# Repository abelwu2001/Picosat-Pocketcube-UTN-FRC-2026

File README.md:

# PocketQube PoCat: análisis, ensayos y propuestas de mejora

Este repositorio reúne la documentación, los diseños electrónicos y los resultados del estudio del satélite **PocketQube PoCat**. El trabajo parte de un diseño existente y busca identificar mejoras comprobables mediante simulaciones, mediciones y comparaciones con la versión original.

> [!IMPORTANT]
> Antes de modificar una placa, hay que confirmar su revisión, función, compatibilidad mecánica y relación con las demás placas del satélite. Todos los cambios deben realizarse sobre una copia del diseño original.

## Objetivos del proyecto

- Comprender el funcionamiento completo del PocketQube.
- Identificar la función y las conexiones de cada placa.
- Reunir los resultados obtenidos por los desarrolladores del diseño original.
- Detectar limitaciones reales mediante mediciones o simulaciones.
- Seleccionar una mejora técnicamente justificable.
- Comparar el comportamiento del diseño original con el modificado.
- Documentar el procedimiento y los resultados para que puedan reproducirse.

## Configuración del satélite

### Placas y elementos principales

| Carpeta o placa | Función principal | Uso en la configuración |
|---|---|---|
| `pq_obc_comms` | Computadora de a bordo y comunicación LoRa | Se utiliza |
| `pq_eps` | Gestión de energía, MPPT, batería y distribución de tensiones | Se utiliza |
| `pq_adcs` | Determinación y control de actitud | A seleccionar (hay dos para eligir) |
| `pq_ymag_board` | Magnetorquer del eje Y | Se utiliza |
| `pq_latboard` | Placas laterales con panel solar y sensores; una incorpora la antena | Se utilizan varias unidades |
| `pq_botboard` | Placa inferior, panel solar, batería, umbilical y *killswitches* | Se utiliza |
| `pq_botnotsobot` | Placa inferior deslizante o estructural del conjunto | Se utiliza |
| `pq_pl1` | Payload de cámara VGA | A seleccionar |
| `pq_pl2` | Payload de detección RFI en banda L | A seleccionar |
| `pq_topboard` | Placa superior genérica | Alternativa al payload, según la configuración |
| `pq_egse` | Equipo eléctrico de apoyo y pruebas en tierra | No vuela |
| `assembly` | Modelos y archivos del ensamblaje mecánico | Solo documentación/diseño |

> [!WARNING]
> Puede cambiar.

## Orden funcional del sistema

El recorrido general de energía, control y datos puede resumirse así:

1. Los paneles solares entregan energía a la `pq_eps`.
2. La EPS administra la carga de la batería y alimenta las demás placas.
3. La `pq_obc_comms` controla el satélite y transmite o recibe información.
4. La `pq_adcs` mide y controla la orientación mediante sensores y magnetorquers.
5. La `pq_pl2` realiza las mediciones de interferencia en banda L.

## Posibles líneas de mejora

### 1. Mejorar el sistema de energía

- Aumentar la eficiencia de los convertidores.
- Revisar el funcionamiento del MPPT.
- Reducir el rizado de las alimentaciones.
- Mejorar el diseño térmico y las pistas de potencia.
- Disminuir las emisiones de las etapas conmutadas.

### 2. Mejorar el sistema de comunicaciones

- Optimizar la adaptación de la antena a `50 Ω`.
- Revisar la pista RF y su camino de retorno.
- Reducir armónicos del transmisor.
- Mejorar el mecanismo de despliegue.
- Comparar alcance, potencia y sensibilidad.

### 3. Mejorar el control de actitud

- Calibrar magnetómetro, giróscopo y sensores solares.
- Filtrar ruido y deriva de los sensores.
- Mejorar el algoritmo de estimación y control.
- Optimizar el accionamiento de los magnetorquers.
- Evitar que las bobinas interfieran con el magnetómetro.

### 4. Reducir interferencias electromagnéticas

- Medir el piso de ruido de PL2 en forma aislada.
- Encender cada subsistema por separado para identificar la fuente de ruido.
- Revisar planos de masa y caminos de retorno.
- Agregar filtros, ferritas, desacoplos o blindaje cuando corresponda.
- Evaluar una ventana silenciosa de medición mediante firmware.
- Comparar los espectros antes y después de la modificación.

### 5. Mejorar el payload de cámara

- Aumentar resolución o calidad de imagen.
- Reducir el consumo entre capturas.
- Incorporar memoria o compresión.
- Mejorar el protocolo de transferencia.

## Links de trabajo 

> [!NOTE]
> **Links**
>
> ```text
> Note one:
> Trello: 
> Drive:
> ```

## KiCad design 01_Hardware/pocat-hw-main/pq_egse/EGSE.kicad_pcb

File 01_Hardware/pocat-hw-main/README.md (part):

# IEEE Open PocketQube Kit – Hardware necesario

Este documento resume las placas, elementos estructurales,
componentes externos, cableado y tornillería necesarios para
el armado de la plataforma PocketQube.

> Nota:
> No se incluyen aquí payloads específicos de las variantes
> demostradoras de la Wiki. La carga útil se considera un
> subsistema independiente/custom.
>
> Las cantidades se basan principalmente en la documentación
> de montaje y hardware del IEEE Open PocketQube Kit.
> Algunas revisiones del repositorio y de la Wiki presentan
> pequeñas diferencias, por lo que siempre debe comprobarse
> la revisión final de PCB antes de comprar componentes.

Link de la wiki donde se explica todo sobre el proyecto:
 
>https://wiki.nanosatlab.space/shelves/ieee-open-pocketqube-kit-mFR

Link BOM final

>https://docs.google.com/spreadsheets/d/18evn2hEh3wvYzuJMzKZhzkFULgpysAK2np7i2tM_1j0/edit?gid=1567048071#gid=1567048071

# 1. PLACAS PCB

## 1.1 Placas del PocketQube

| **Cantidad** | **Placa** | **Función** |
|---:|---|---|
| 1 | **PQ_ADCS_HBridge** | Control de actitud: recibe sensores y maneja los magnetorquers mediante puentes H. |
| 1 | **PQ_EPS** | Sistema de potencia: recibe energía solar, carga la batería y distribuye las tensiones del satélite. |
| 1 | **pq_obc_comms** | Computadora principal + comunicaciones por radio con tierra. |
| 1 | **pq_topboard** | Cara superior estructural e interfaz de la zona del payload. |
| 1 | **pq_botboard** | Cara inferior; integra celda solar, sensores y un magnetorquer eje -Y PCB. |
| 4 | **pq_latboard** | Caras laterales +X, -X, +Z y -Z. Integran celda solar, sensores y magnetorquer; una lleva además la antena COMMS. |
| 1 | **PQ_MagYBoard** | Magnetorquer interno dedicado al eje +Y. |
| 1 | **pq_botnotsobot** | Placa mecánica asociada al sliding/deployer y al sistema de despliegue. |
| **11** | **Total PCBs del conjunto** | Sin contar payload custom ni EGSE. |

### Magnetorquers

El PocketQube utiliza **6 magnetorquers**:

- 4 integrados en las `pq_latboard`
- 1 integrado en la `pq_botboard`
- 1 en la `PQ_MagYBoard`

Los magnetorquers integrados en las placas se forman mediante
pistas/bobinas de cobre del propio PCB, por lo que no se compran
como componentes independientes.

## 1.2 Placa de soporte en tierra

## Cableado e interconexiones

| ID | From | Num. of cables | Connector | To | Num. of cables | Connector | Length (mm) |
|---:|---|---:|---|---|---:|---|---:|
| 1 | Lat +Z | 10 | PicoBlade | PCB Connector | 10 | PicoBlade | |
| 2 | PCB Connector | 10 | PicoBlade | ADCS | 10 | PicoClasp | |
| 3 | Lat -Z | 10 | PicoBlade | PCB Connector | 10 | PicoBlade | |
| 4 | PCB Connector | 10 | PicoBlade | ADCS | 10 | PicoClasp | |
| 5 | Lat +X | 10 | PicoBlade | PCB Connector | 10 | PicoBlade | |
| 6 | PCB Connector | 10 | PicoBlade | ADCS | 10 | PicoClasp | |
| 7 | Lat -X | 10 | PicoBlade | PCB Connector | 10 | PicoBlade | |
| 8 | PCB Connector | 10 | PicoBlade | ADCS | 10 | PicoClasp | |
| 9 | Battery | 2 | PicoBlade | - | - | - | |
| 10 | PCB Connector | 2 | PicoBlade | Bottom Board | 2 | PicoBlade | |
| 11 | Battery Heater & NTC | 3 | PicoClasp | - | - | - | |
| 12 | PCB Connector | 3 | PicoClasp | ADCS | 3 | PicoClasp | |
| 13 | Umbilical | 8 | PicoBlade | PCB Connector | 8 | PicoBlade | |
| 14 | Bottom Board | 15 | PicoBlade | PCB Connector | 15 | PicoBlade | |
| 15 | PCB Connector | 15 | PicoBlade | ADCS | 15 | PicoClasp | |
| 16 | Top Board | 9 | PicoBlade | PCB Connector | 9 | PicoBlade | |
| 17 | PCB Connector | 9 | PicoBlade | ADCS | 9 | PicoClasp | |

La EGSE no forma parte del hardware de vuelo. Se utiliza en banco
para alimentación, mediciones, depuración e integración.

Por lo tanto:

- PCBs del PocketQube: 11
- PCB EGSE: 1
- Total a fabricar si se realiza todo el conjunto: 12

# 2. BATERÍA

| Cantidad | Elemento | Especificación |
|---:|---|---|
| 1 | Batería Li-ion | 3.7 V |
| 1 | Capacidad nominal | 1400 mAh |
| 1 | Energía nominal | 5.18 Wh |
| 1 | Modelo indicado en Assembly Wiki | 103540 |

La batería se instala dentro de la estructura inferior.

IMPORTANTE:
La documentación del proyecto posee revisiones que mencionan
otras baterías. Para este listado se conserva la especificación
indicada en la página de Assembly de la Wiki.

# 3. CELDAS SOLARES

Modelo indicado:

Lightricity S3040_CIC

Características aproximadas indicadas en la Wiki:

- Tecnología: Triple Junction GaAs
- Integración: CIC
- Dimensiones: 40.15 x 30.35 x 0.30 mm
- Área fotovoltaica activa: 12 cm²
- Tensión AM0: ~2.5 V
- Potencia AM0: ~0.5 W

## Cantidad

| Ubicación | Cantidad |
|---|---:|
| Lateral +X | 1 |
| Lateral -X | 1 |
| Lateral +Z | 1 |
| Lateral -Z | 1 |
| Bottom board | 1 |
| **TOTAL** | **5** |

La plataforma utiliza:

**5 x Lightricity S3040_CIC**

La cara superior/payload no lleva celda solar en esta
configuración de la Wiki.

# 4. FOTODIODOS

Modelo indicado:

**SLCD-61N8 – Advanced Photonix**

La arquitectura ADCS utiliza un fotodiodo en cada cara para
determinar la incidencia de radiación solar.

| Ubicación | Cantidad |
|---|---:|
| Cuatro lateral boards | 4 |
| Top board | 1 |
| Bottom board | 1 |
| **TOTAL** | **6** |

Cantidad a comprar:

**6 x SLCD-61N8**

Datos principales indicados en la documentación:

- Isc aproximada: 170 µA
- Voc aproximada: 0.4 V
- Máxima sensibilidad: 930 nm
- Acceptance Half Angle: 60°

# 5. SENSORES DE TEMPERATURA

Modelo:

**TCN75A / TCN75AVOA – Microchip**

La Wiki especifica un sensor de temperatura en cada placa
lateral.

Cantidad mínima documentada para las caras laterales:

**4 x TCN75A**

Características:

- Interfaz: I2C
- Rango: -40 °C a +125 °C
- Precisión: aproximadamente ±1 °C
- Bajo consumo

Verificar en la BOM final de `topboard` y `botboard` si la
revisión fabricada incorpora sensores de temperatura
adicionales.

# 6. KILLSWITCHES

El PocketQube utiliza:

**2 x killswitches**

Los dos interruptores están conectados en serie para proporcionar
redundancia.

Su función es mantener desconectada la batería mientras el
PocketQube se encuentra dentro del deployer.

Cuando el PocketQube es liberado:

1. los killswitches dejan de estar presionados;
2. se habilita la alimentación;
3. comienza la secuencia de encendido.

IMPORTANTE:
La Wiki de Assembly los describe asociados a la estructura/PCB
inferior. El repositorio también contiene `pq_botnotsobot`,
relacionado con la interfaz de despliegue. Confirmar la ubicación
mecánica exacta con la revisión final que se vaya a fabricar.

# 7. SISTEMA DE ANTENA COMMS

Se necesita una placa lateral configurada para comunicaciones.

Elementos principales:

| Cantidad | Elemento |
|---:|---|
| 1 | Antena desplegable de cinta metálica |
| 1 | Cable RF desde OBC-COMMS |
| 1 | Dyneema / UHMWPE |
| 1 | Resorte de extensión |
| 1 | Jumper SMT de guiado |
| 2 | Resistencias thermal-knife |
| 1 | Cable clip / sujeción de antena |
| 2 | Tornillos M2.5 asociados al mecanismo |
| según diseño | Inserts/elementos de fijación |

## Dyneema

Especificación indicada:

- UHMWPE
- diámetro: 0.35 mm
- resistencia aproximada: 26 kg

La documentación de mantenimiento utiliza aproximadamente
40 cm para realizar el montaje, dejando excedente para los
nudos.

## Resorte

Modelo indicado:

**McMaster-Carr 5108N98**

Su función es mantener tensión constante sobre el Dyneema.

## Jumper SMT

Modelo indicado:

**Harwin S1731-46R**

Se utiliza como guía y para mantener el Dyneema en contacto con
los thermal knives.

## Thermal knives

La revisión actual de la página del deployer utiliza:

**2 x resistencias de baja impedancia**

Valor actualmente indicado:

**4.7 ohm**

Estas resistencias son calentadas eléctricamente mediante
`BURNCOMMS`, cortando/fundiendo el Dyneema y permitiendo que la
antena se despliegue.

IMPORTANTE:
Documentación anterior de mantenimiento menciona 7.5 ohm.
Comprobar siempre el esquemático de la revisión fabricada antes
de comprar las resistencias.

# 8. CABLEADO INTERNO

## Laterales ↔ ADCS

Cantidad:

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
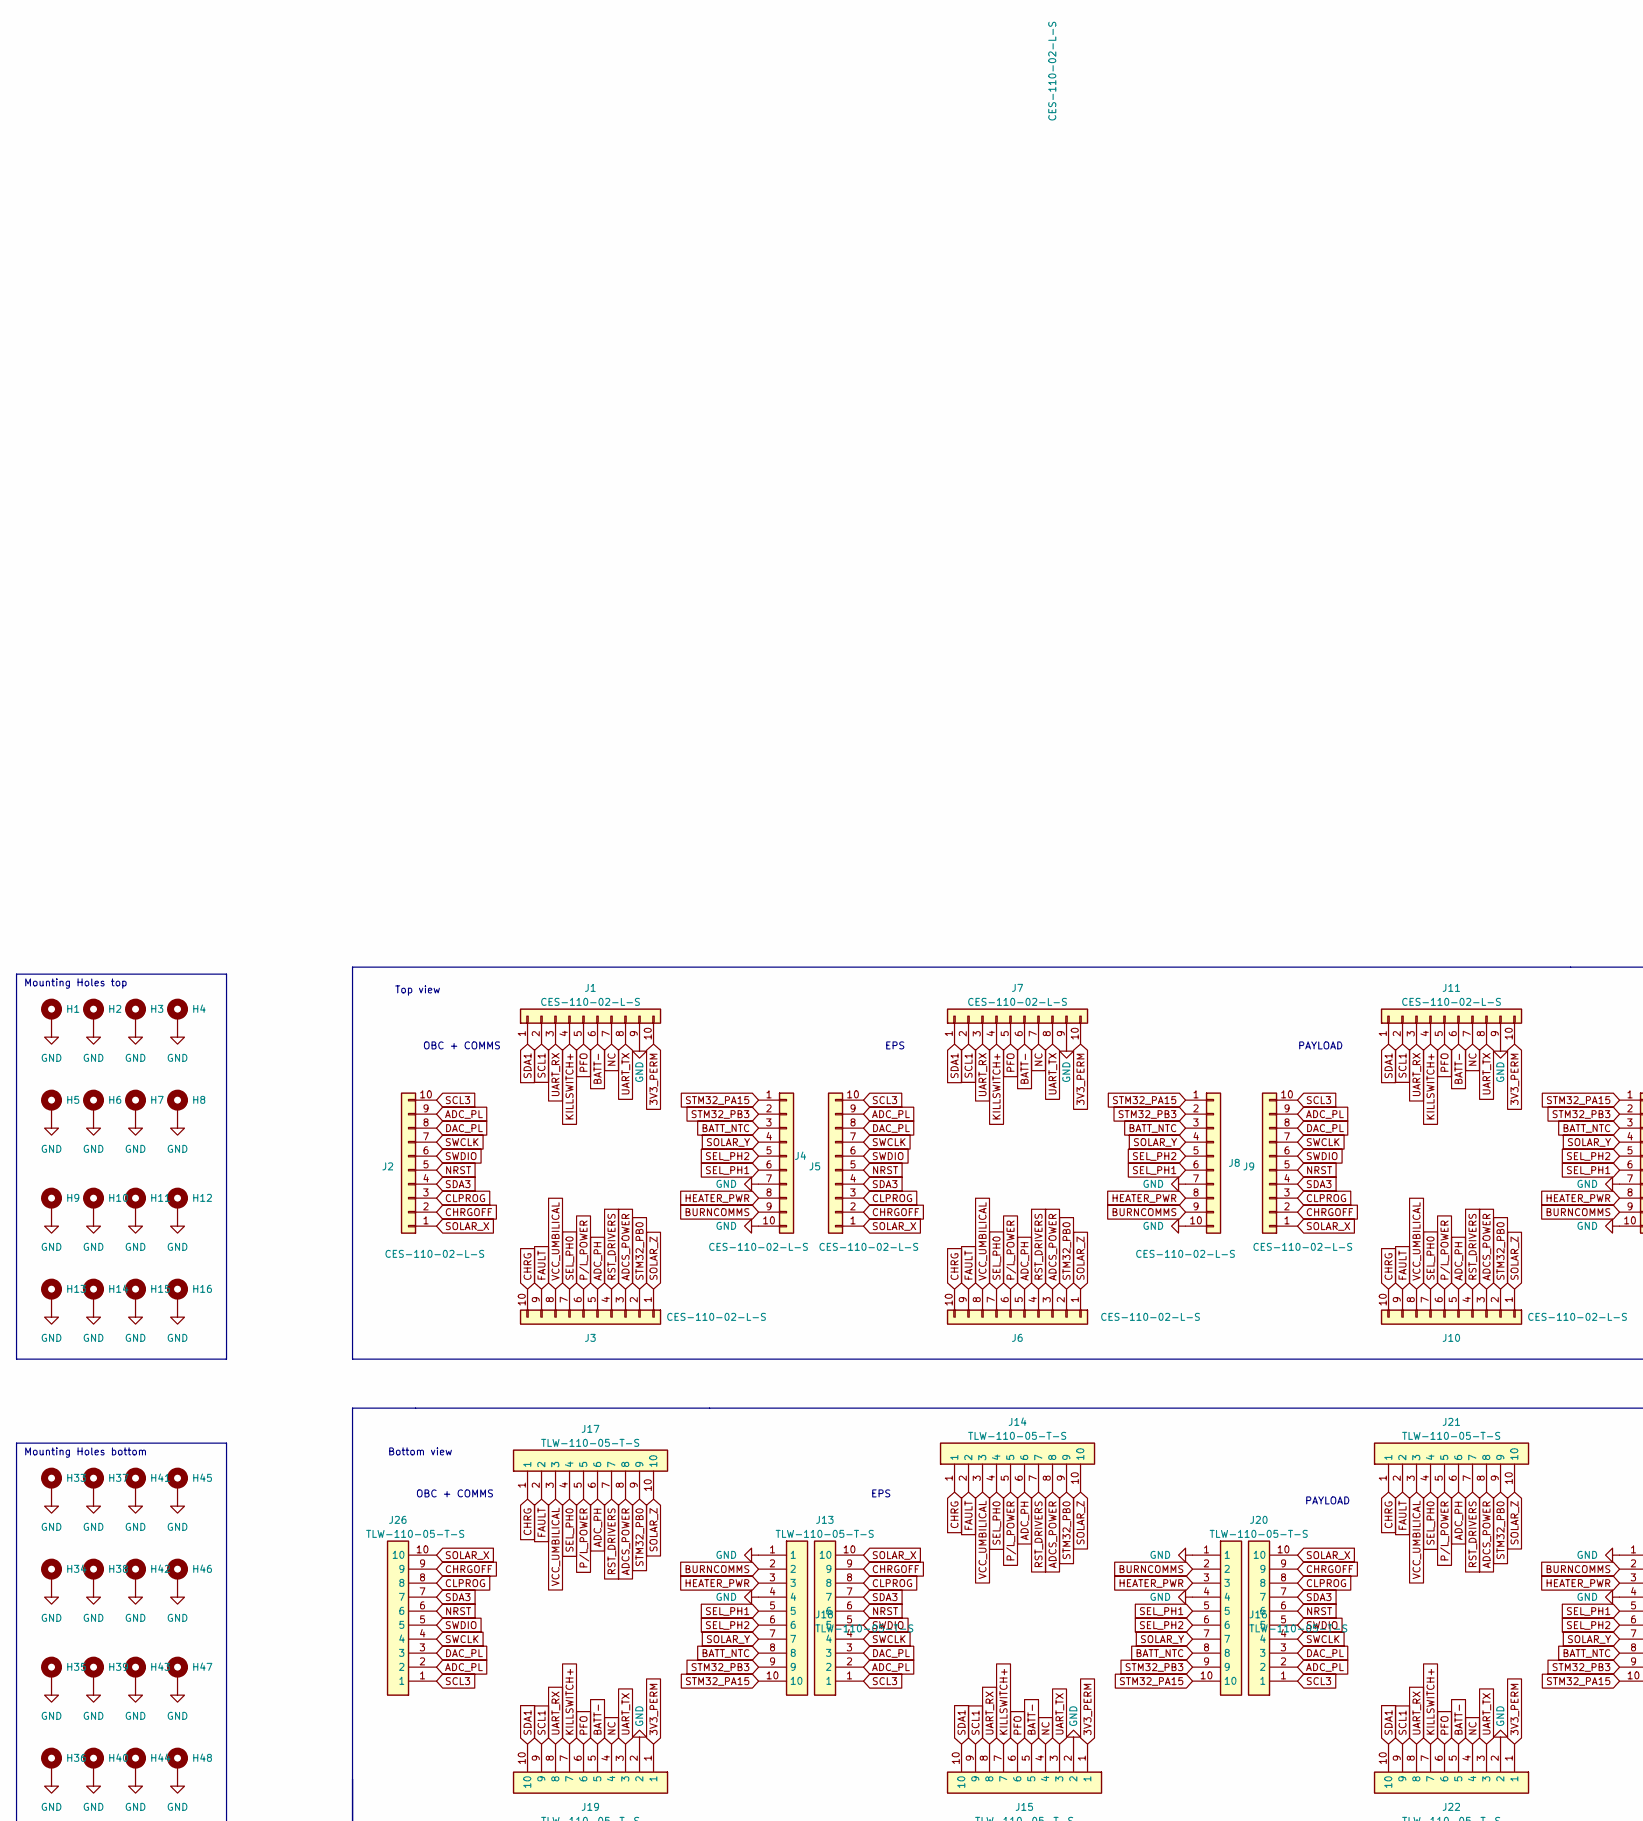
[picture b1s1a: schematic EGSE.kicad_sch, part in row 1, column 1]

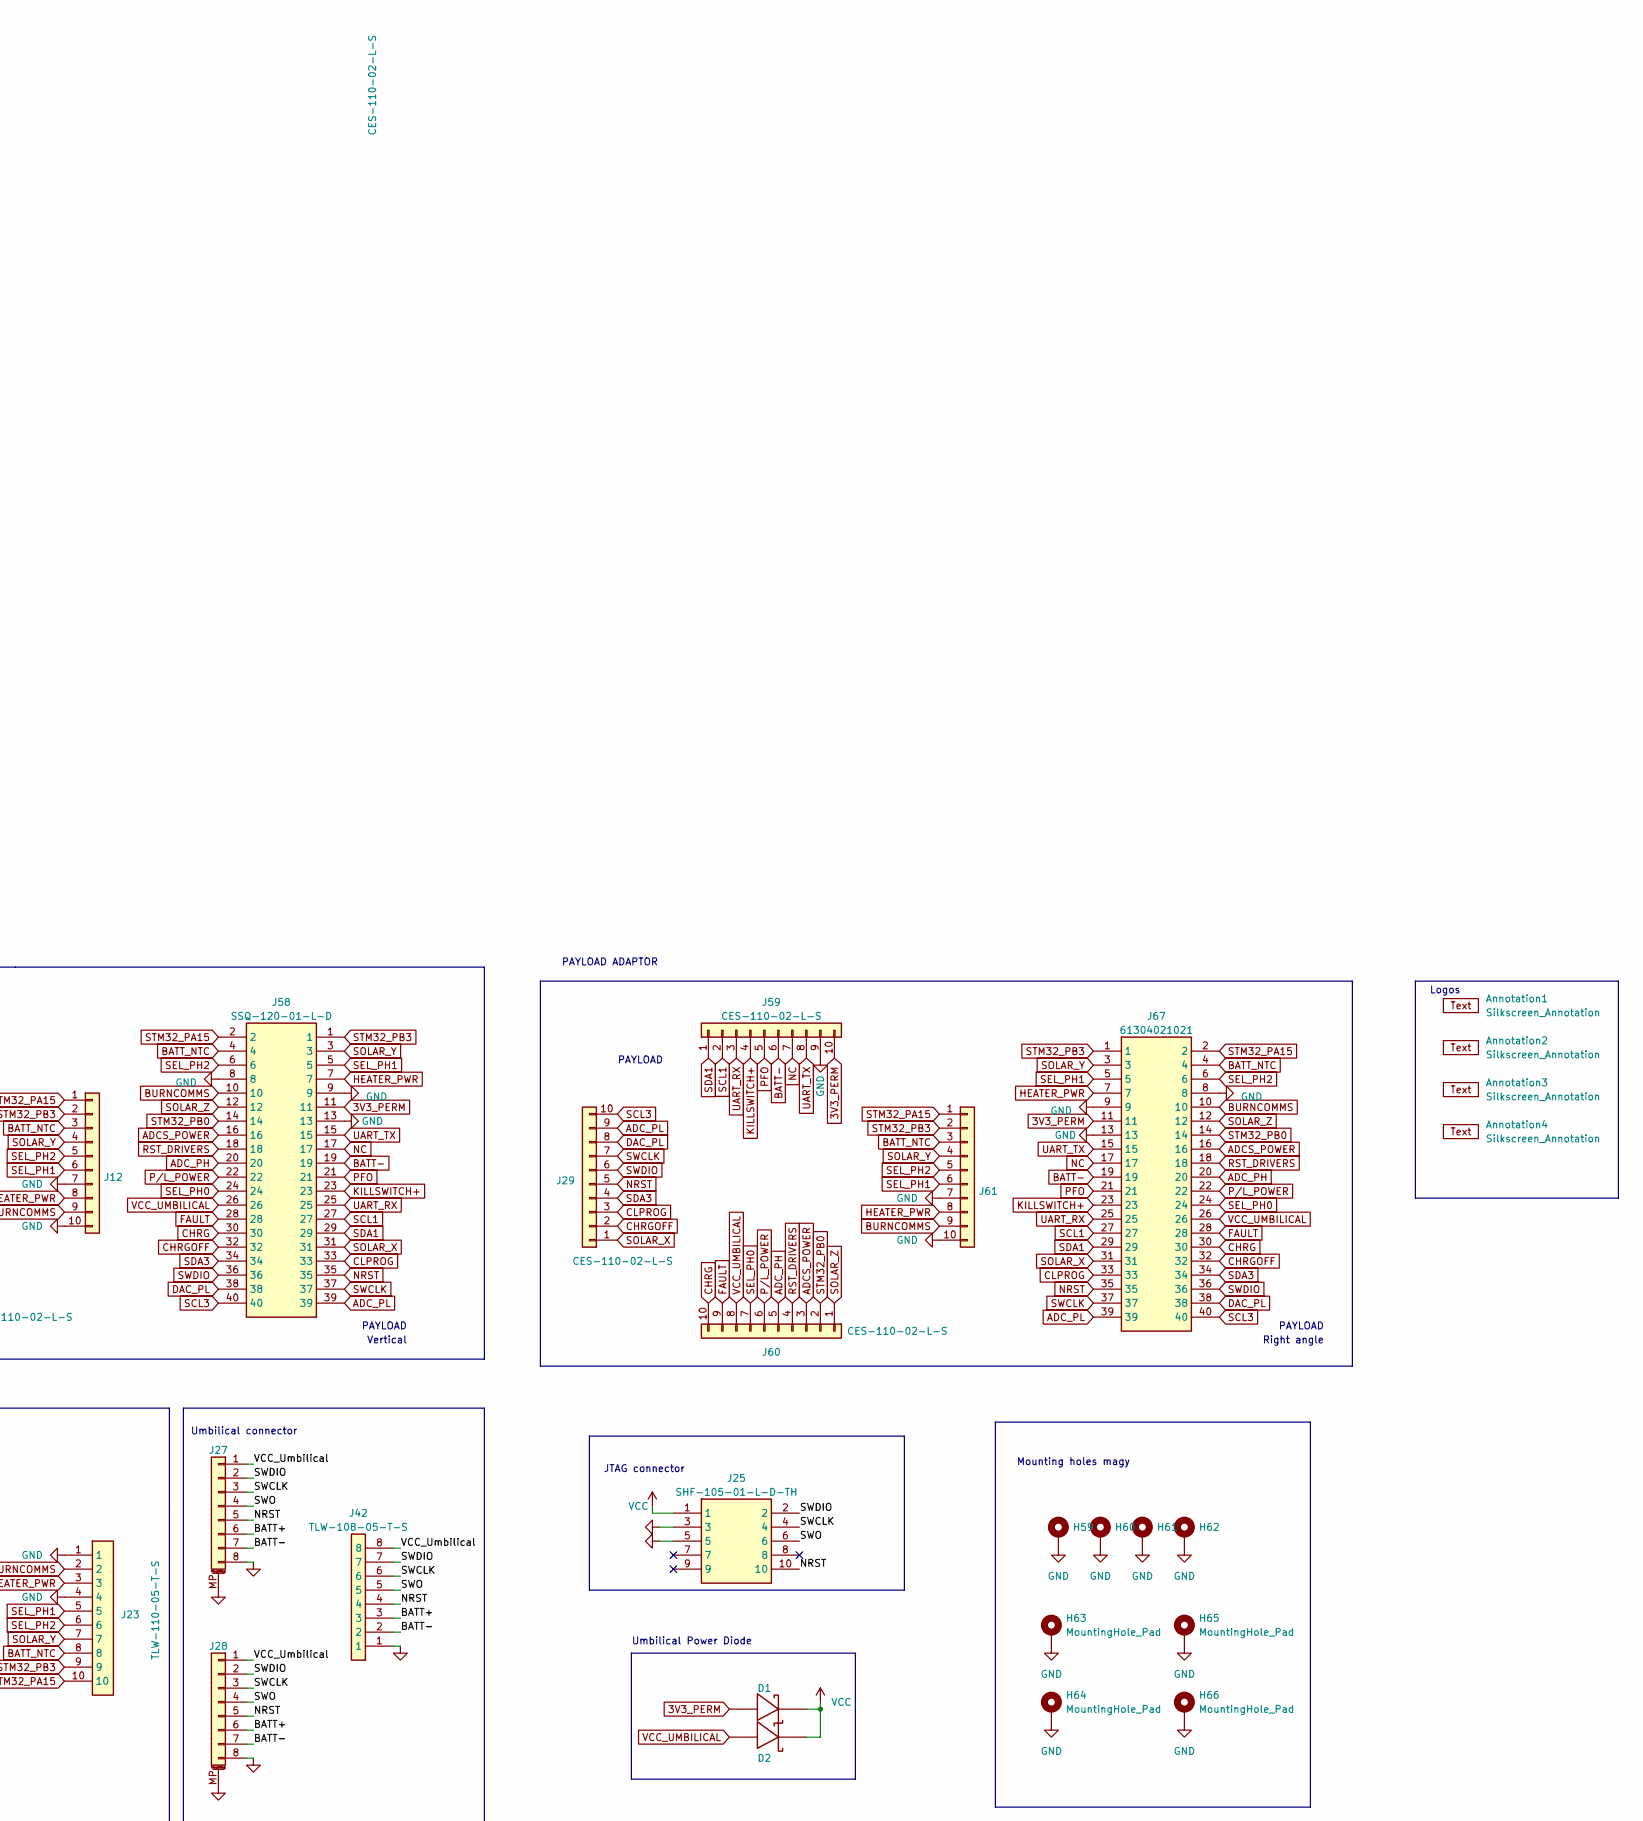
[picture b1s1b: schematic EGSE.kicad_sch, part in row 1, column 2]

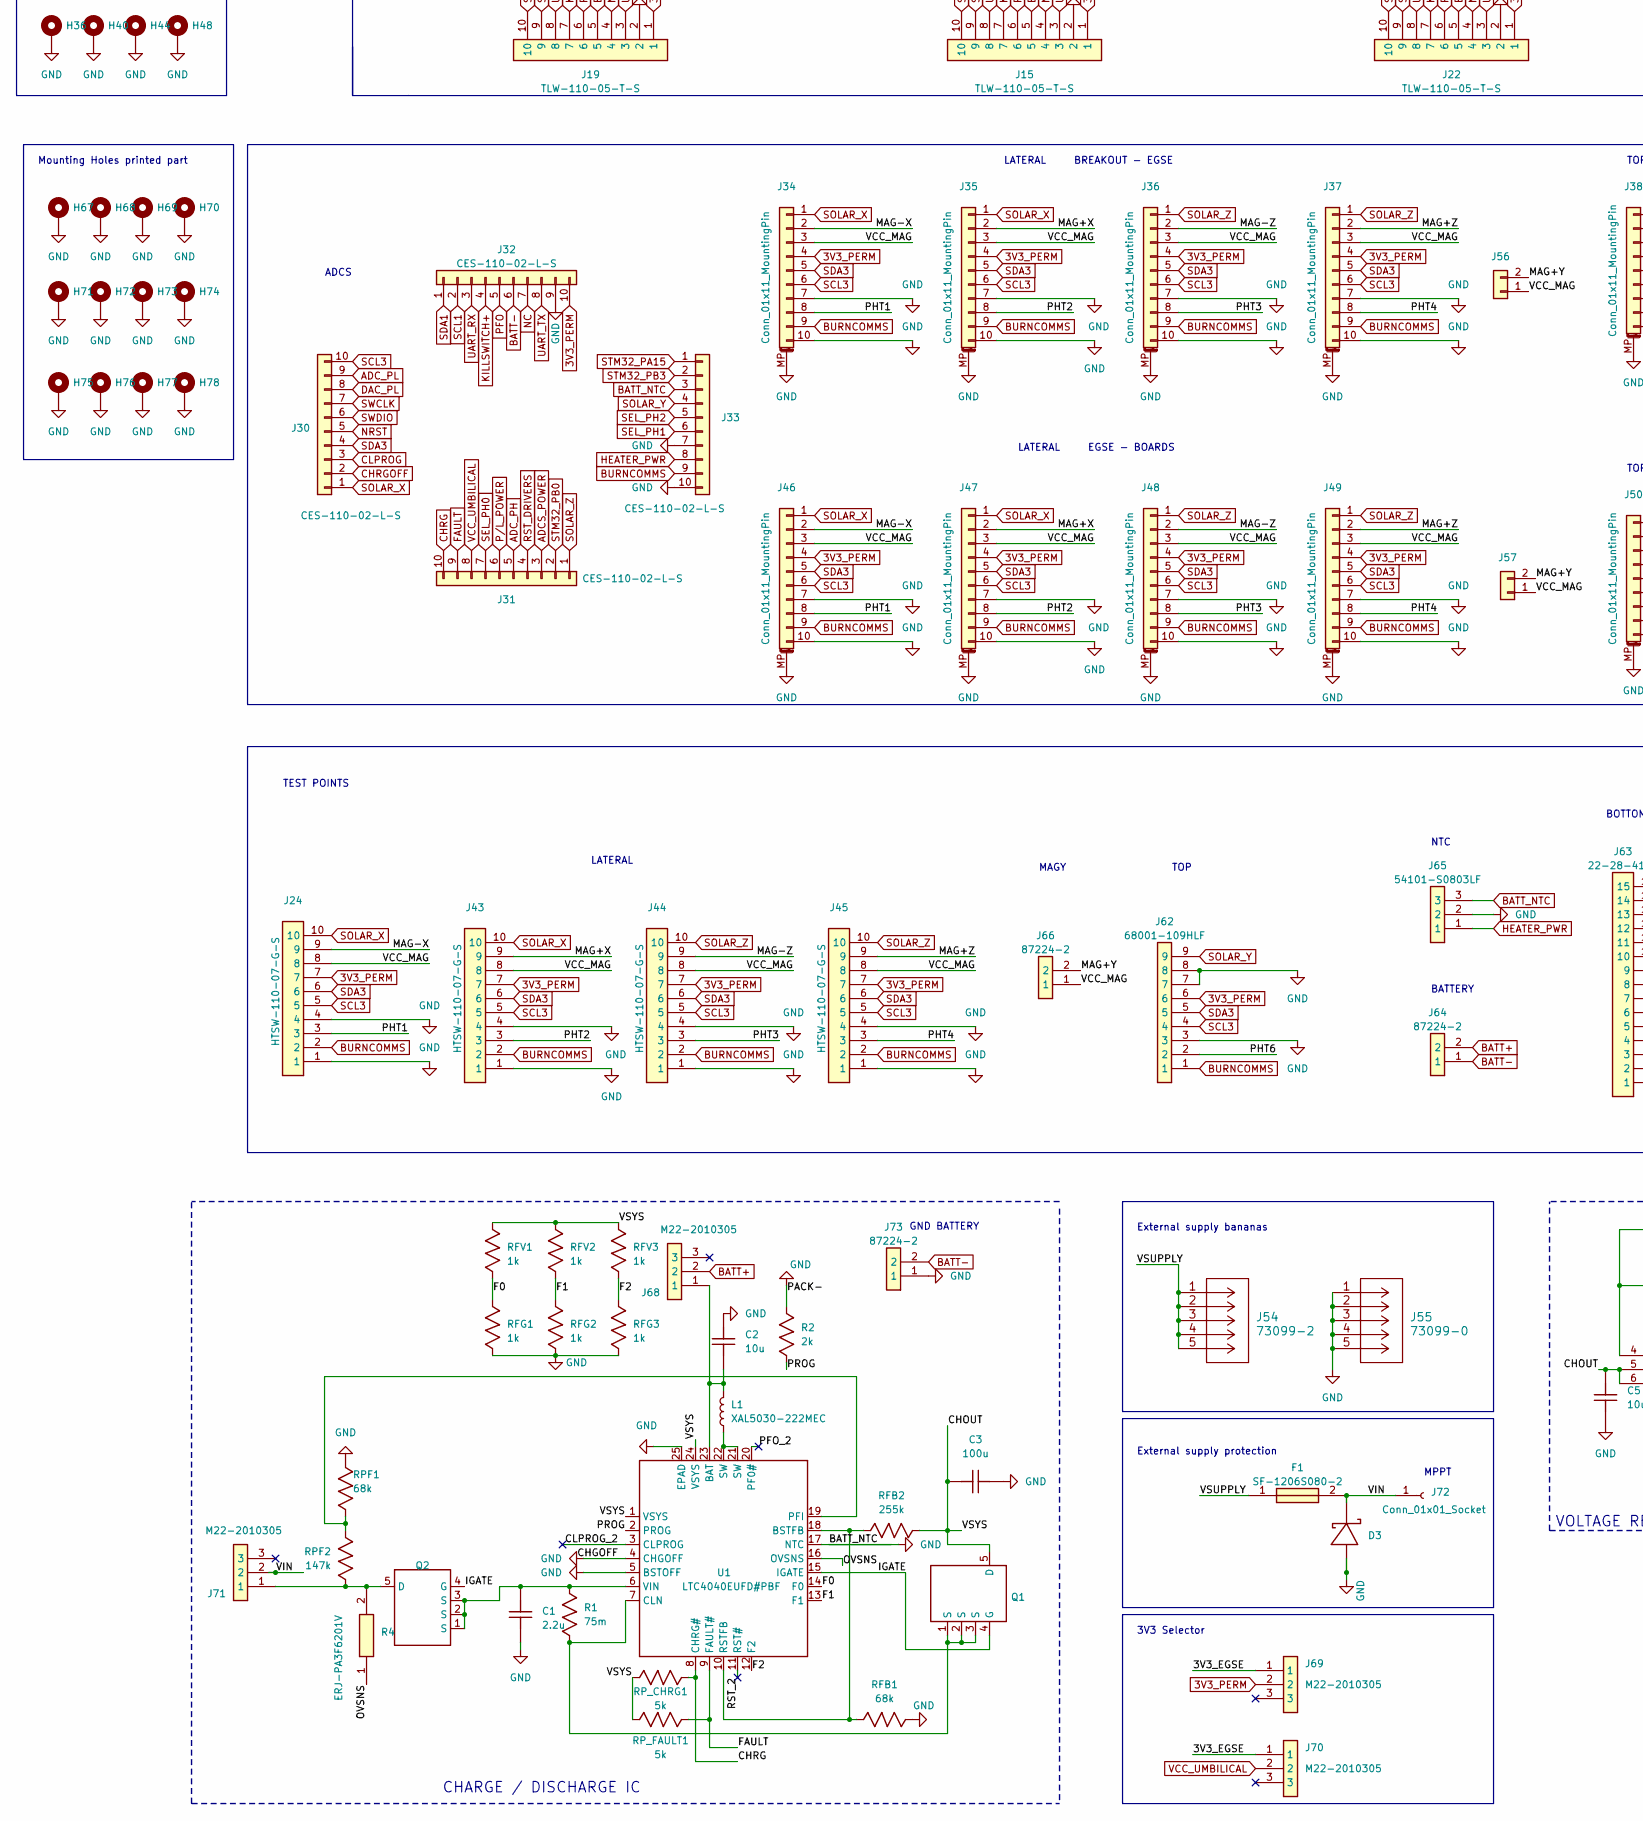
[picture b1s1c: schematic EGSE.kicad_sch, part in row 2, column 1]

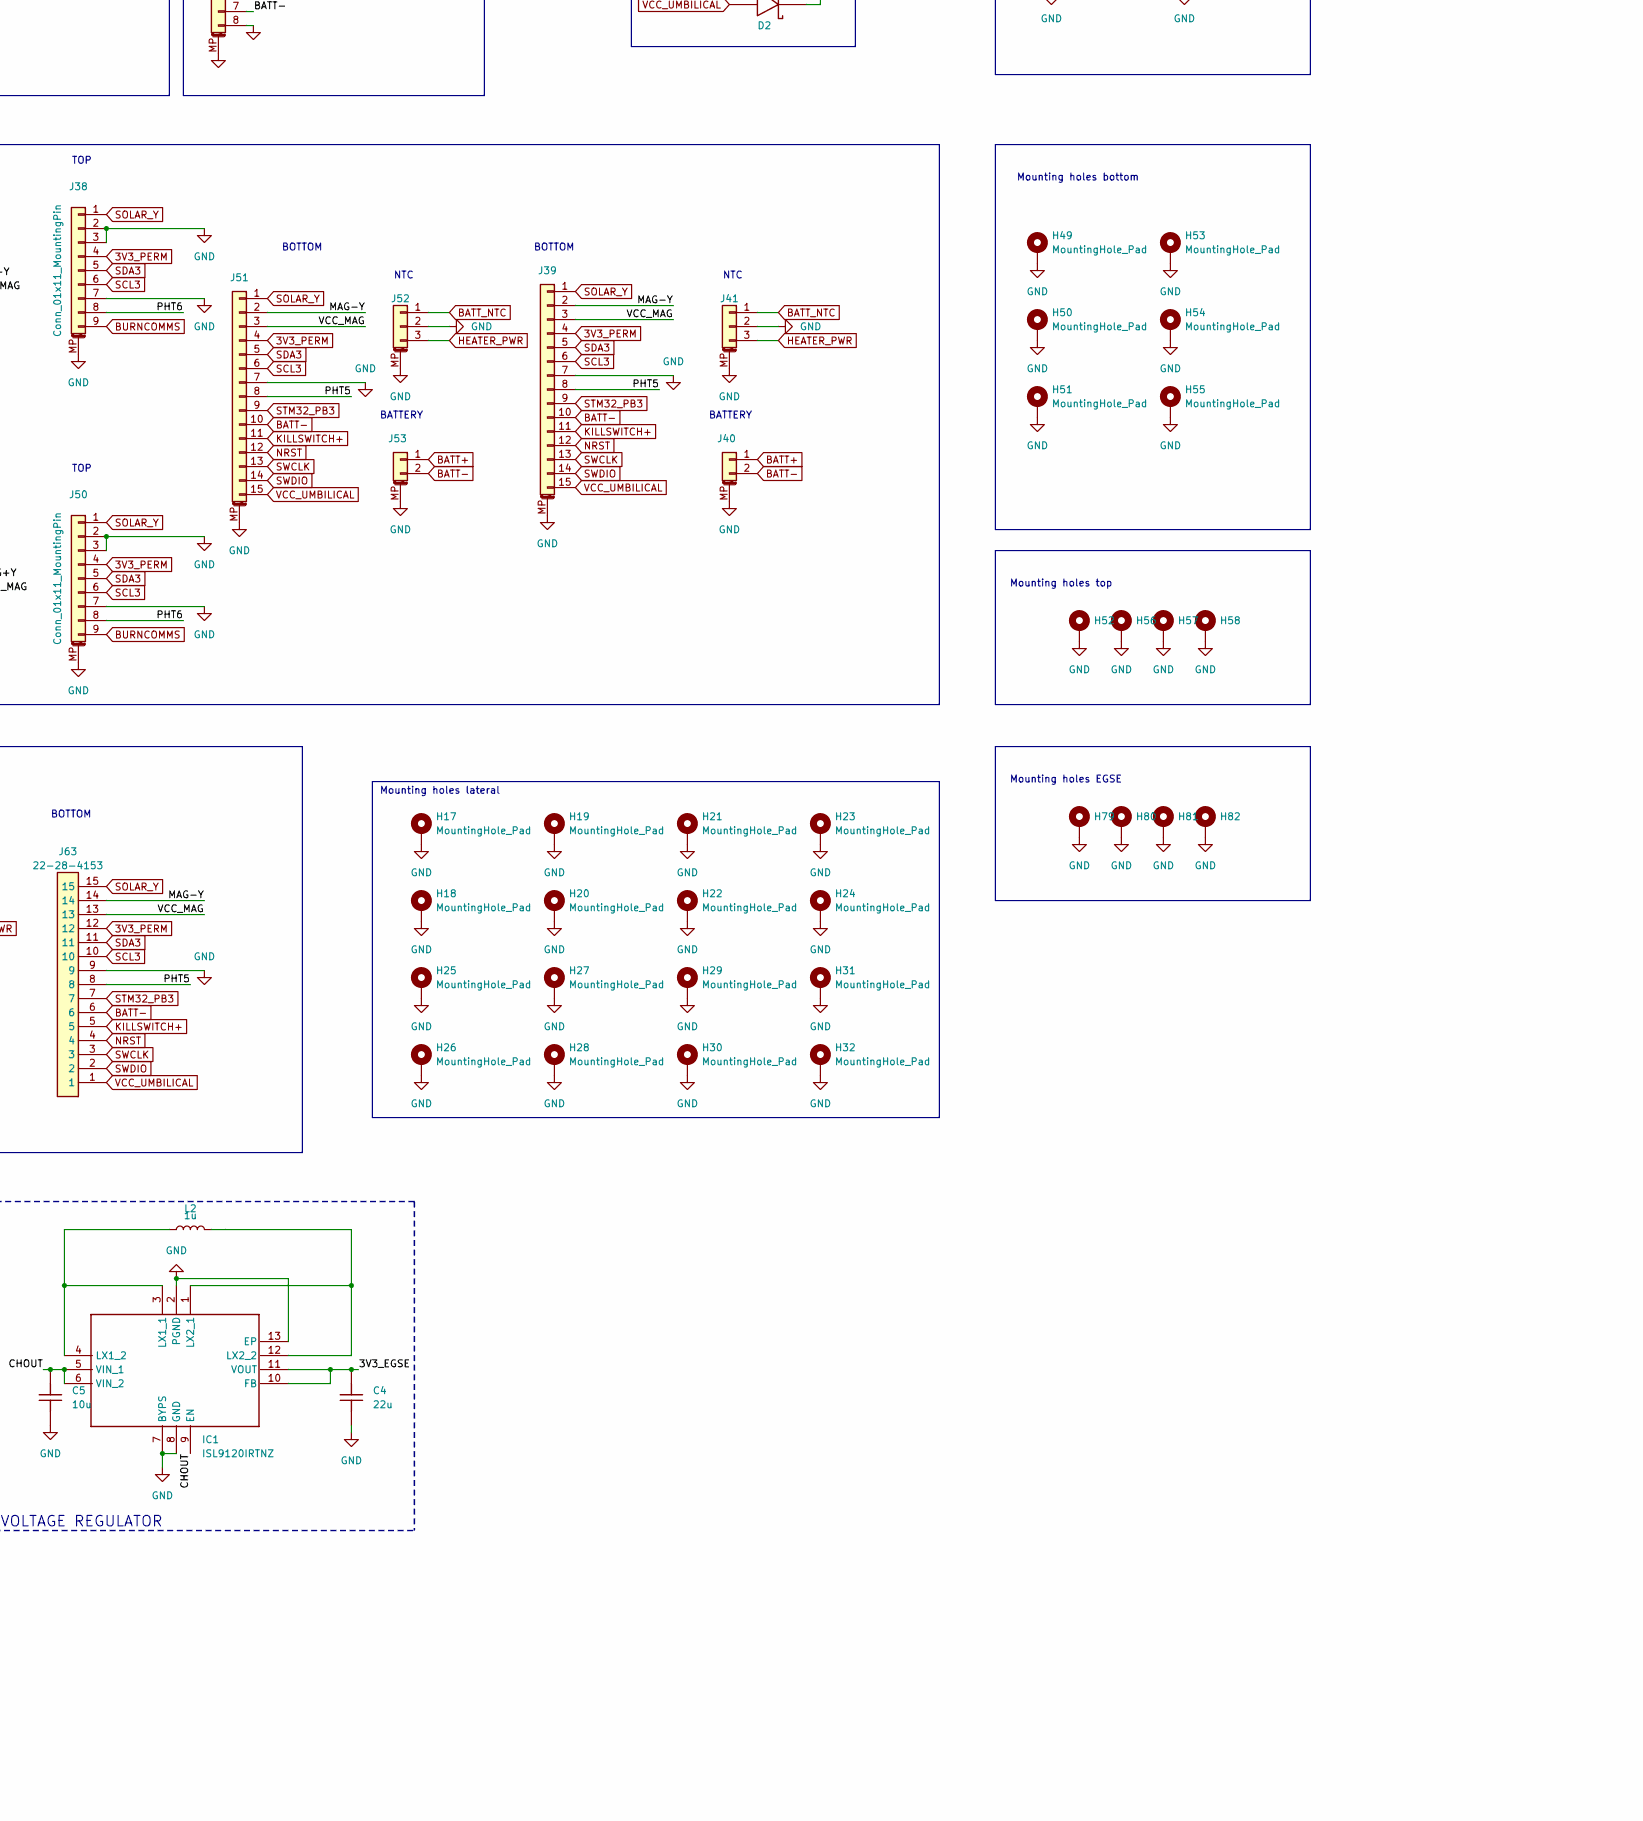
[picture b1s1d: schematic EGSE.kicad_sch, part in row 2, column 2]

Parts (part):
Annotation1: Silkscreen_Annotation; Bridgemaker__Annotation1
Annotation2: Silkscreen_Annotation; IEEE_logo__Annotation2
Annotation3: Silkscreen_Annotation; NSL_long__Annotation3
Annotation4: Silkscreen_Annotation; Telecos__Annotation4
C1: 2.2u; C_0603_1608Metric__C1
C2: 10u; C_0603_1608Metric__C2
C3: 100u; C_1206_3216Metric__C3
C4: 22u; C_0603_1608Metric__C4
C5: 10u; C_0603_1608Metric__C5
D1, D2, D3: type="D" model="RBS1LAM40ATR" lib=""; RBS1LAM40ATR_Schottky; Manufacturer Part Numbe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 RBS1LAM40ATR
F1: SF-1206S080-2; FUSC3116X70N__F1; Mouser Part Number 652-SF-1206S080-2
H1: MountingHole_Pad; MountingHole_3.2mm_M3_Pad__H1
H2: MountingHole_Pad; MountingHole_3.2mm_M3_Pad__H2
H3: MountingHole_Pad; MountingHole_3.2mm_M3_Pad__H3
H4: MountingHole_Pad; MountingHole_3.2mm_M3_Pad__H4
H5: MountingHole_Pad; MountingHole_3.2mm_M3_Pad__H5
H6: MountingHole_Pad; MountingHole_3.2mm_M3_Pad__H6
H7: MountingHole_Pad; MountingHole_3.2mm_M3_Pad__H7
H8: MountingHole_Pad; MountingHole_3.2mm_M3_Pad__H8
H9: MountingHole_Pad; MountingHole_3.2mm_M3_Pad__H9
H10: MountingHole_Pad; MountingHole_3.2mm_M3_Pad__H10
H11: MountingHole_Pad; MountingHole_3.2mm_M3_Pad__H11
H12: MountingHole_Pad; MountingHole_3.2mm_M3_Pad__H12
H13: MountingHole_Pad; MountingHole_3.2mm_M3_Pad__H13
H14: MountingHole_Pad; MountingHole_3.2mm_M3_Pad__H14
H15: MountingHole_Pad; MountingHole_3.2mm_M3_Pad__H15
H16: MountingHole_Pad; MountingHole_3.2mm_M3_Pad__H16
H17, H18, H19, H20, H21, H22, H23, H24, H25, H26, H27, H28, H29, H30, H31, H32, H49, H50, H51, H53, H54, H55, H63, H64, H65, H66: MountingHole_Pad; MountingHole_2.2mm_M2_Pad
H33, H34, H35, H36, H37, H38, H39, H40, H41, H42, H43, H44, H45, H46, H47, H48, H52, H56, H57, H58, H59, H60, H67, H70, H71, H72, H73, H74, H75, H76, H77, H78, H79, H80, H81, H82: MountingHole_Pad; MountingHole_3.2mm_M3_Pad
H61: MountingHole_Pad; MountingHole_3.2mm_M3_Pad__H61
H62: MountingHole_Pad; MountingHole_3.2mm_M3_Pad__H62
H68: MountingHole_Pad; MountingHole_3.2mm_M3_Pad__H68
H69: MountingHole_Pad; MountingHole_3.2mm_M3_Pad__H69
IC1: ISL9120IRTNZ
J1: CES-110-02-L-S; PinSocket_1x10_P2.54mm_Vertical__J1; Manufacturer Part Numbe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 CES-110-02-L-S
J2: CES-110-02-L-S; PinSocket_1x10_P2.54mm_Vertical__J2; Manufacturer Part Numbe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 CES-110-02-L-S
J3: CES-110-02-L-S; PinSocket_1x10_P2.54mm_Vertical__J3; Manufacturer Part Numbe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 CES-110-02-L-S
J4: CES-110-02-L-S; PinSocket_1x10_P2.54mm_Vertical__J4; Manufacturer Part Numbe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 CES-110-02-L-S
J5: CES-110-02-L-S; PinSocket_1x10_P2.54mm_Vertical__J5; Manufacturer Part Numbe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 CES-110-02-L-S
J6: CES-110-02-L-S; PinSocket_1x10_P2.54mm_Vertical__J6; Manufacturer Part Numbe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 CES-110-02-L-S
J7: CES-110-02-L-S; PinSocket_1x10_P2.54mm_Vertical__J7; Manufacturer Part Numbe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 CES-110-02-L-S
J8: CES-110-02-L-S; PinSocket_1x10_P2.54mm_Vertical__J8; Manufacturer Part Numbe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 CES-110-02-L-S
J9: CES-110-02-L-S; PinSocket_1x10_P2.54mm_Vertical__J9; Manufacturer Part Numbe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 CES-110-02-L-S
J10: CES-110-02-L-S; PinSocket_1x10_P2.54mm_Vertical__J10; Manufacturer Part Numbe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 CES-110-02-L-S
J11: CES-110-02-L-S; PinSocket_1x10_P2.54mm_Vertical__J11; Manufacturer Part Numbe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 CES-110-02-L-S
J12: CES-110-02-L-S; PinSocket_1x10_P2.54mm_Vertical__J12; Manufacturer Part Numbe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 CES-110-02-L-S
J13: TLW-110-05-T-S; HDRV10W64P0X254_1X10_2540X248X838P__J13; Mouser Part Number 200-HTSW11007GS
J14: TLW-110-05-T-S; HDRV10W64P0X254_1X10_2540X248X838P__J14; Mouser Part Number 200-HTSW11007GS
J15: TLW-110-05-T-S; HDRV10W64P0X254_1X10_2540X248X838P__J15; Mouser Part Number 200-HTSW11007GS
J16: TLW-110-05-T-S; HDRV10W64P0X254_1X10_2540X248X838P__J16; Mouser Part Number 200-HTSW11007GS
J17: TLW-110-05-T-S; HDRV10W64P0X254_1X10_2540X248X838P__J17; Mouser Part Number 200-HTSW11007GS
J18: TLW-110-05-T-S; HDRV10W64P0X254_1X10_2540X248X838P__J18; Mouser Part Number 200-HTSW11007GS
J19: TLW-110-05-T-S; HDRV10W64P0X254_1X10_2540X248X838P__J19; Mouser Part Number 200-HTSW11007GS
J20: TLW-110-05-T-S; HDRV10W64P0X254_1X10_2540X248X838P__J20; Mouser Part Number 200-HTSW11007GS
J21: TLW-110-05-T-S; HDRV10W64P0X254_1X10_2540X248X838P__J21; Mouser Part Number 200-HTSW11007GS
J22: TLW-110-05-T-S; HDRV10W64P0X254_1X10_2540X248X838P__J22; Mouser Part Number 200-HTSW11007GS
J23: TLW-110-05-T-S; HDRV10W64P0X254_1X10_2540X248X838P__J23; Mouser Part Number 200-HTSW11007GS
J24: HTSW-110-07-G-S; HDRV10W64P0X254_1X10_2540X248X838P__J24; Mouser Part Number 200-HTSW11007GS
J25: SHF-105-01-L-D-TH; SHF10501LDTH__J25; Mouser Part Number 200-SHF10501LDTH
J26: TLW-110-05-T-S; HDRV10W64P0X254_1X10_2540X248X838P__J26; Mouser Part Number 200-HTSW11007GS
J27: Conn_01x08_MountingPin; Molex_PicoBlade_53398-0871_1x08-1MP_P1.25mm_Vertical__J27
J28: Conn_01x08_MountingPin; Molex_PicoBlade_53398-0871_1x08-1MP_P1.25mm_Vertical__J28
J29: CES-110-02-L-S; PinSocket_1x10_P2.54mm_Vertical__J29; Manufacturer Part Numbe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 CES-110-02-L-S
J30: CES-110-02-L-S; PinSocket_1x10_P2.54mm_Vertical__J30; Manufacturer Part Numbe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 CES-110-02-L-S
J31: CES-110-02-L-S; PinSocket_1x10_P2.54mm_Vertical__J31; Manufacturer Part Numbe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 CES-110-02-L-S
J32: CES-110-02-L-S; PinSocket_1x10_P2.54mm_Vertical__J32; Manufacturer Part Numbe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 CES-110-02-L-S
J33: CES-110-02-L-S; PinSocket_1x10_P2.54mm_Vertical__J33; Manufacturer Part Numbe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 CES-110-02-L-S
J34: Conn_01x11_MountingPin; Molex_PicoBlade_53261-1071_1x10-1MP_P1.25mm_Horizontal__J34
J35: Conn_01x11_MountingPin; Molex_PicoBlade_53261-1071_1x10-1MP_P1.25mm_Horizontal__J35
J36: Conn_01x11_MountingPin; Molex_PicoBlade_53261-1071_1x10-1MP_P1.25mm_Horizontal__J36
J37: Conn_01x11_MountingPin; Molex_PicoBlade_53261-1071_1x10-1MP_P1.25mm_Horizontal__J37
J38: Conn_01x11_MountingPin; Molex_PicoBlade_53261-0971_1x09-1MP_P1.25mm_Horizontal__J38
J39: 53261-1471; Molex_PicoBlade_53261-1571_1x15-1MP_P1.25mm_Horizontal__J39
J40: 53261-0271; Molex_PicoBlade_53261-0271_1x02-1MP_P1.25mm_Horizontal__J40
J41: Pico-Clasp_01x03; Picoclasp03__J41; Manufacturer Part Numbe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 203556-0307
J42: TLW-108-05-T-S; SAMTEC_TLW-108-05-T-S__J42; Mouser Part Number 200-TLW10805TS
J43: HTSW-110-07-G-S; HDRV10W64P0X254_1X10_2540X248X838P__J43; Mouser Part Number 200-HTSW11007GS
J44: HTSW-110-07-G-S; HDRV10W64P0X254_1X10_2540X248X838P__J44; Mouser Part Number 200-HTSW11007GS
J45: HTSW-110-07-G-S; HDRV10W64P0X254_1X10_2540X248X838P__J45; Mouser Part Number 200-HTSW11007GS
J46: Conn_01x11_MountingPin; Molex_PicoBlade_53261-1071_1x10-1MP_P1.25mm_Horizontal__J46
J47: Conn_01x11_MountingPin; Molex_PicoBlade_53261-1071_1x10-1MP_P1.25mm_Horizontal__J47
J48: Conn_01x11_MountingPin; Molex_PicoBlade_53261-1071_1x10-1MP_P1.25mm_Horizontal__J48
J49: Conn_01x11_MountingPin; Molex_PicoBlade_53261-1071_1x10-1MP_P1.25mm_Horizontal__J49
J50: Conn_01x11_MountingPin; Molex_PicoBlade_53261-0971_1x09-1MP_P1.25mm_Horizontal__J50
J51: 53261-1471; Molex_PicoBlade_53261-1571_1x15-1MP_P1.25mm_Horizontal__J51
J52: Pico-Clasp_01x03; Picoclasp03__J52; Manufacturer Part Numbe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 203556-0307
J53: 53261-0271; Molex_PicoBlade_53261-0271_1x02-1MP_P1.25mm_Horizontal__J53
J54: 73099-2; 73099-2__J54
J55: 73099-0; 73099-2__J55
J56: CES-102-02-L-S; CES-102-02__J56; Manufacturer Part Numbe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 CES-102-02-L-S
J57: CES-102-02-L-S; CES-102-02__J57; Manufacturer Part Numbe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 CES-102-02-L-S
J58: SSQ-120-01-L-D; SSQ-120-XX-YYY-D__J58; Mouser Part Number 200-SSQ12001LD
J59: CES-110-02-L-S; PinSocket_1x10_P2.54mm_Vertical__J59; Manufacturer Part Numbe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 CES-110-02-L-S
J60: CES-110-02-L-S; PinSocket_1x10_P2.54mm_Vertical__J60; Manufacturer Part Numbe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 CES-110-02-L-S
J61: CES-110-02-L-S; PinSocket_1x10_P2.54mm_Vertical__J61; Manufacturer Part Numbe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 CES-110-02-L-S
J62: 68001-109HLF; HDRV9W90P0X254_1X9_2286X241X1143P__J62; Mouser Part Number 649-68001-109HLF
J63: 22-28-4153; HDRV15W66P0X254_1X15_3810X249X838P__J63; Mouser Part Number 538-22-28-4153
J64: 87224-2; 872242__J64; Mouser Part Number 571-872242
J65: 54101-S0803LF; 54101S0803LF__J65; Mouser Part Number 649-54101-S0803LF
J66: 87224-2; 872242__J66; Mouser Part Number 571-872242
J67: 61304021021; HDRRA40W64P254_2X20_5080X254X508P__J67; Mouser Part Number 710-61304021021
J68: M22-2010305; HDRV3W60P0X200_1X3_600X200X525P__J68; Mouser Part Number 855-M22-2010305
J69: M22-2010305; HDRV3W60P0X200_1X3_600X200X525P__J69; Mouser Part Number 855-M22-2010305
J70: M22-2010305; HDRV3W60P0X200_1X3_600X200X525P__J70; Mouser Part Number 855-M22-2010305
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
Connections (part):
3V3_PERM: D1.2, J1.10, J7.10, J11.10, J15.1, J19.1, J22.1, J24.7, J32.10, J34.4, J35.4, J36.4, J37.4, J38.4, J39.4, J43.7, J44.7, J45.7, J46.4, J47.4, J48.4, J49.4, J50.4, J51.4, J58.11, J59.10, J62.6, J63.12, J67.11, J69.2
/3V3_EGSE: C4.2, IC1.10 (FB), IC1.11 (VOUT), J69.1, J70.1
/CHOUT: C3.1, C5.2, IC1.5 (VIN_1), IC1.6 (VIN_2), IC1.9 (EN), Q1.5 (D), RFB2.2, RFV1.2, RFV2.2, RFV3.2, RP_CHRG1.2, RP_FAULT1.2, U1.1 (VSYS), U1.24 (VSYS)
/CLPROG_2: U1.3 (CLPROG)
/F0: RFG1.2, RFV1.1, U1.14 (F0)
/F1: RFG2.2, RFV2.1, U1.13 (F1)
/F2: RFG3.2, RFV3.1, U1.12 (F2)
/IGATE: Q1.4 (G), Q2.4 (G), U1.15 (IGATE)
/MAG+X: J35.2, J43.9, J47.2
/MAG+Y: J56.2, J57.2, J66.2
/MAG+Z: J37.2, J45.9, J49.2
/MAG-X: J24.9, J34.2, J46.2
/MAG-Y: J39.2, J51.2, J63.14
/MAG-Z: J36.2, J44.9, J48.2
/OVSNS: R4.1, U1.16 (OVSNS)
/PFO_2: U1.20 (PF0#)
/PHT1: J24.3, J34.8, J46.8
/PHT2: J35.8, J43.3, J47.8
/PHT3: J36.8, J44.3, J48.8
/PHT4: J37.8, J45.3, J49.8
/PHT5: J39.8, J51.8, J63.8
/PHT6: J38.8, J50.8, J62.2
/PROG: R2.1, U1.2 (PROG)
/RST_2: U1.11 (RST#)
/SWO: J25.6, J27.4, J28.4, J42.5
/VCC_MAG: J24.8, J34.3, J35.3, J36.3, J37.3, J39.3, J43.8, J44.8, J45.8, J46.3, J47.3, J48.3, J49.3, J51.3, J56.1, J57.1, J63.13, J66.1
/VCC_Umbilical: J27.1, J28.1, J42.8
/VIN: D3.1, F1.2, J71.2, J72.1
/VSUPPLY: F1.1, J54.1, J54.2, J54.3, J54.4, J54.5
ADCS_POWER: J3.3, J6.3, J10.3, J14.8, J17.8, J21.8, J31.3, J58.16, J60.3, J67.16
ADC_PH: J3.5, J6.5, J10.5, J14.6, J17.6, J21.6, J31.5, J58.20, J60.5, J67.20
ADC_PL: J2.9, J5.9, J9.9, J13.2, J20.2, J26.2, J29.9, J30.9, J58.39, J67.39
BATT+: J27.6, J28.6, J40.1, J42.3, J53.1, J64.2, J68.2
BATT-: J1.6, J7.6, J11.6, J15.5, J19.5, J22.5, J27.7, J28.7, J32.6, J39.10, J40.2, J42.2, J51.10, J53.2, J58.19, J59.6, J63.6, J64.1, J67.19, J73.2
BATT_NTC: J4.3, J8.3, J12.3, J16.8, J18.8, J23.8, J33.3, J41.1, J52.1, J58.4, J61.3, J65.3, J67.4
BURNCOMMS: J4.9, J8.9, J12.9, J16.2, J18.2, J23.2, J24.2, J33.9, J34.9, J35.9, J36.9, J37.9, J38.9, J43.2, J44.2, J45.2, J46.9, J47.9, J48.9, J49.9, J50.9, J58.10, J61.9, J62.1, J67.10
CHRG: J3.10, J6.10, J10.10, J14.1, J17.1, J21.1, J31.10, J58.30, J60.10, J67.30, RP_CHRG1.1, U1.8 (CHRG#)
CHRGOFF: J2.2, J5.2, J9.2, J13.9, J20.9, J26.9, J29.2, J30.2, J58.32, J67.32
CLPROG: J2.3, J5.3, J9.3, J13.8, J20.8, J26.8, J29.3, J30.3, J58.33, J67.33
DAC_PL: J2.8, J5.8, J9.8, J13.3, J20.3, J26.3, J29.8, J30.8, J58.38, J67.38
FAULT: J3.9, J6.9, J10.9, J14.2, J17.2, J21.2, J31.9, J58.28, J60.9, J67.28, RP_FAULT1.1, U1.9 (FAULT#)
GND: C1.2, C2.2, C3.2, C4.1, C5.1, D3.2, H1.1, H2.1, H3.1, H4.1, H5.1, H6.1, H7.1, H8.1, H9.1, H10.1, H11.1, H12.1, H13.1, H14.1, H15.1, H16.1, H17.1, H18.1, H19.1, H20.1, H21.1, H22.1, H23.1, H24.1, H25.1, H26.1, H27.1, H28.1, H29.1, H30.1, H31.1, H32.1, H33.1, H34.1, H35.1, H36.1, H37.1, H38.1, H39.1, H40.1, H41.1, H42.1, H43.1, H44.1, H45.1, H46.1, H47.1, H48.1, H49.1, H50.1, H51.1, H52.1, H53.1, H54.1, H55.1, H56.1, H57.1, H58.1, H59.1, H60.1, H61.1, H62.1, H63.1, H64.1, H65.1, H66.1, H67.1, H68.1, H69.1, H70.1, H71.1, H72.1, H73.1, H74.1, H75.1, H76.1, H77.1, H78.1, H79.1, H80.1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
HEATER_PWR: J4.8, J8.8, J12.8, J16.3, J18.3, J23.3, J33.8, J41.3, J52.3, J58.7, J61.8, J65.1, J67.7
KILLSWITCH+: J1.4, J7.4, J11.4, J15.7, J19.7, J22.7, J32.4, J39.11, J51.11, J58.23, J59.4, J63.5, J67.23
NC: J1.7, J7.7, J11.7, J15.4, J19.4, J22.4, J32.7, J58.17, J59.7, J67.17
NRST: J2.5, J5.5, J9.5, J13.6, J20.6, J25.10, J26.6, J27.5, J28.5, J29.5, J30.5, J39.12, J42.4, J51.12, J58.35, J63.4, J67.35
unnamed: IC1.3 (LX1_1), IC1.4 (LX1_2), L2.1
unnamed: IC1.1 (LX2_1), IC1.12 (LX2_2), L2.2
unnamed: L1.1, U1.21 (SW), U1.22 (SW)
unnamed: J71.1, Q2.5 (D), R4.2, RPF2.1
unnamed: C2.1, J68.1, L1.2, U1.23 (BAT)
unnamed: RFB1.1, RFB2.1, U1.10 (RSTFB), U1.18 (BSTFB)
unnamed: Q1.1 (S), Q1.2 (S), Q1.3 (S), R1.1, U1.7 (CLN)
unnamed: RPF1.1, RPF2.2, U1.19 (PFI)
unnamed: C1.1, Q2.1 (S), Q2.2 (S), Q2.3 (S), R1.2, U1.6 (VIN)
PFO: J1.5, J7.5, J11.5, J15.6, J19.6, J22.6, J32.5, J58.21, J59.5, J67.21
P/L_POWER: J3.6, J6.6, J10.6, J14.5, J17.5, J21.5, J31.6, J58.22, J60.6, J67.22
RST_DRIVERS: J3.4, J6.4, J10.4, J14.7, J17.7, J21.7, J31.4, J58.18, J60.4, J67.18
SCL1: J1.2, J7.2, J11.2, J15.9, J19.9, J22.9, J32.2, J58.27, J59.2, J67.27
SCL3: J2.10, J5.10, J9.10, J13.1, J20.1, J24.5, J26.1, J29.10, J30.10, J34.6, J35.6, J36.6, J37.6, J38.6, J39.6, J43.5, J44.5, J45.5, J46.6, J47.6, J48.6, J49.6, J50.6, J51.6, J58.40, J62.4, J63.10, J67.40
SDA1: J1.1, J7.1, J11.1, J15.10, J19.10, J22.10, J32.1, J58.29, J59.1, J67.29
SDA3: J2.4, J5.4, J9.4, J13.7, J20.7, J24.6, J26.7, J29.4, J30.4, J34.5, J35.5, J36.5, J37.5, J38.5, J39.5, J43.6, J44.6, J45.6, J46.5, J47.5, J48.5, J49.5, J50.5, J51.5, J58.34, J62.5, J63.11, J67.34
SEL_PH0: J3.7, J6.7, J10.7, J14.4, J17.4, J21.4, J31.7, J58.24, J60.7, J67.24
SEL_PH1: J4.6, J8.6, J12.6, J16.5, J18.5, J23.5, J33.6, J58.5, J61.6, J67.5
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
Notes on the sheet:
BATTERY
PAYLOAD
TEST POINTS
Logos
ADCS
GND BATTERY
3V3 Selector
CHARGE / DISCHARGE IC
JTAG connector
Mounting holes top
EPS
LATERAL
Vertical
PAYLOAD
BOTTOM
Mounting holes EGSE
Umbilical connector
TOP
Bottom view
OBC + COMMS
Umbilical Power Diode
PAYLOAD ADAPTOR
VOLTAGE REGULATOR
Top view
External supply protection
MAGY
External supply bananas
EGSE - BOARDS
NTC
EPS
Mounting holes magy
BREAKOUT - EGSE
Mounting holes bottom
Mounting Holes bottom
Mounting Holes top
OBC + COMMS
Mounting Holes printed part
MPPT
Mounting holes lateral
Right angle

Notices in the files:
parts and their libraries:
Copyright 2021 Accelerated Designs. All rights reserved.
